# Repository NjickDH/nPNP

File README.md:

# nPNP

## Description
This project will aim to build a high speed and accurate pick and place machine using bldc motors as servo's, automatic feeders and vision. Currently work is being done on developing component feeders.

## Features
- __Automatic component feeders:__
  - Designed for use of tape with 8mm Tape and Reel specifications.
  - Uses a 40x40mm aluminium profile as rail for mounting with integrated usb port for automatic powering and communication with the feeders.
  - Capable of accepting 20 feeders on a 500mm long aluminium profile.
  - SMT Reel holder which makes use of full sized reels convenient.
  - Handle for ease of insertion/removal from aluminium rail.
  - UART over RS485 for easy and reliable communication with the feeders. This means all feeders are controllable using a single USB port with use of a USB-RS485 converter.
  - Two buttons for manual control of the motor driving the tape forwards and backwards.
  - RGB Status LED provides the user with the current status of each feeder.
  - Integrated IR sensor as rotary encoder for accurate repeatability of the motors movement.
  - Automatically and mechanically peels tape based on the movement of the tape itself to reduce complexity and part count.
  - 
-

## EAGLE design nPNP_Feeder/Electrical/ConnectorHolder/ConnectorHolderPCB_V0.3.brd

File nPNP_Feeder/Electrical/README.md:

# nPNP Feeder electrical

## Description
The schematic and board files for all PCB's for each feeder are placed here. Please read relevant notes for each of these boards below.

## Notes
- __MainFeeder:__
  - Schematic has MCU named as ATmega328-AU as this is the highest MCU in the pin compatible series. Actual MCU in the main feeder, and for which the firmware is written, is the ATmega48A. For more information about pin compatibility click [here](https://ww1.microchip.com/downloads/en/DeviceDoc/ATmega48A-PA-88A-PA-168A-PA-328-P-DS-DS40002061B.pdf) .
- __USBFeeder:__
  - This PCB has to be connected to the main feeder PCB by soldering 4 wires from the 4 pads on the USBFeeder PCB to the 4 pads on the main feeder PCB.
- __ConnectorHolder:__
  - This PCB is to be inserted into the 40x40mm aluminium profile. Two holes on each end are used for mounting the PCB inside the slot. An alumium profile with the following dimensions must be used:

### TODO:
- [x] Add BOM for each PCB
- [ ] Add price estimation for each PCB
- [ ] Validate MainFeederV1.0

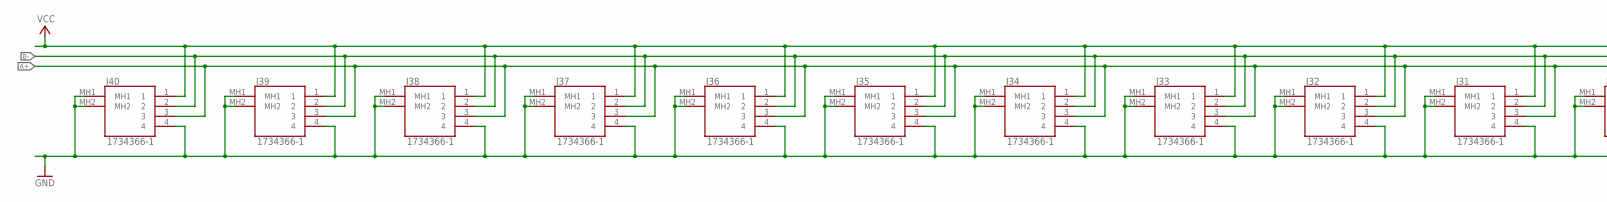
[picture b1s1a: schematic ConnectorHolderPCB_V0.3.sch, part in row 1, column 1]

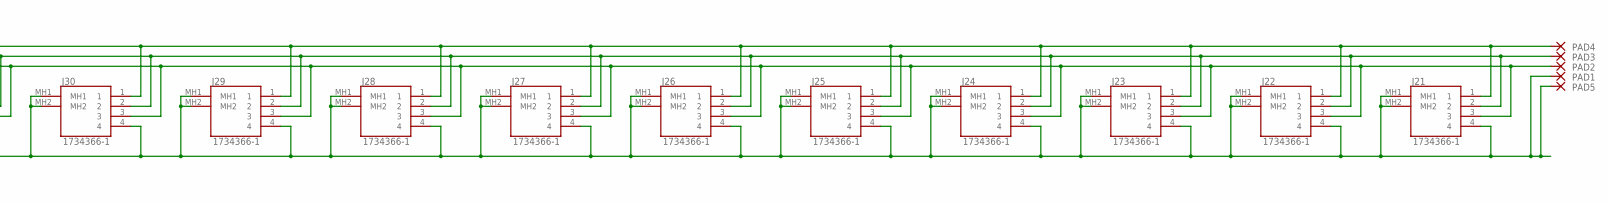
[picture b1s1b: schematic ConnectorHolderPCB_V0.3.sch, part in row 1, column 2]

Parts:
J21, J22, J23, J24, J25, J26, J27, J28, J29, J30, J31, J32, J33, J34, J35, J36, J37, J38, J39, J40: 1734366-1; 17343661
PAD1, PAD2, PAD3, PAD4, PAD5: SMD2; SMD1,27-2,54

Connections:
A+: J21.3, J22.3, J23.3, J24.3, J25.3, J26.3, J27.3, J28.3, J29.3, J30.3, J31.3, J32.3, J33.3, J34.3, J35.3, J36.3, J37.3, J38.3, J39.3, J40.3, PAD2.1
B-: J21.2, J22.2, J23.2, J24.2, J25.2, J26.2, J27.2, J28.2, J29.2, J30.2, J31.2, J32.2, J33.2, J34.2, J35.2, J36.2, J37.2, J38.2, J39.2, J40.2, PAD3.1
GND: J21.4, J21.MH1, J21.MH2, J22.4, J22.MH1, J22.MH2, J23.4, J23.MH1, J23.MH2, J24.4, J24.MH1, J24.MH2, J25.4, J25.MH1, J25.MH2, J26.4, J26.MH1, J26.MH2, J27.4, J27.MH1, J27.MH2, J28.4, J28.MH1, J28.MH2, J29.4, J29.MH1, J29.MH2, J30.4, J30.MH1, J30.MH2, J31.4, J31.MH1, J31.MH2, J32.4, J32.MH1, J32.MH2, J33.4, J33.MH1, J33.MH2, J34.4, J34.MH1, J34.MH2, J35.4, J35.MH1, J35.MH2, J36.4, J36.MH1, J36.MH2, J37.4, J37.MH1, J37.MH2, J38.4, J38.MH1, J38.MH2, J39.4, J39.MH1, J39.MH2, J40.4, J40.MH1, J40.MH2, PAD1.1, PAD5.1
VCC: J21.1, J22.1, J23.1, J24.1, J25.1, J26.1, J27.1, J28.1, J29.1, J30.1, J31.1, J32.1, J33.1, J34.1, J35.1, J36.1, J37.1, J38.1, J39.1, J40.1, PAD4.1

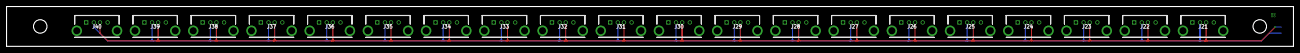
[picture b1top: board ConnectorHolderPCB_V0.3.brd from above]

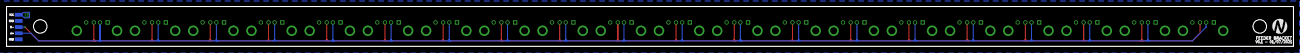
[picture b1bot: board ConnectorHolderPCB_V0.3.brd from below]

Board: 2 copper layers, 420.0 x 13.0 mm, 26 parts (6 on the bottom side), 4 nets.

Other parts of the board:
U$1: NPNP_LARGE_NOTEXT

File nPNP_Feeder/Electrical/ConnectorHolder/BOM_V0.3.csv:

Qty;Value;Device;Package;Parts;Description;DESCRIPTION;HEIGHT;MANUFACTURER_NAME;MANUFACTURER_PART_NUMBER;MOUSER_PART_NUMBER;MOUSER_PRICE-STOCK;POPULARITY
20;1734366-1;1734366-1;17343661;J21, J22, J23, J24, J25, J26, J27, J28, J29, J30, J31, J32, J33, J34, J35, J36, J37, J38, J39, J40;USB Connectors 1PORT 4POS VERT T/H USB 2.0 BLACK;USB Connectors 1PORT 4POS VERT T/H USB 2.0 BLACK;15mm;TE Connectivity;1734366-1;571-1734366-1;https://www.mouser.co.uk/ProductDetail/TE-Connectivity/17343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;

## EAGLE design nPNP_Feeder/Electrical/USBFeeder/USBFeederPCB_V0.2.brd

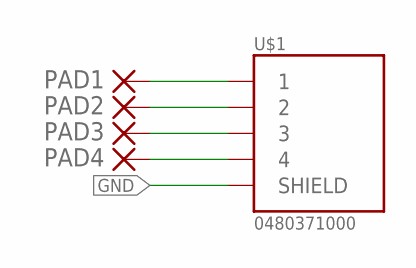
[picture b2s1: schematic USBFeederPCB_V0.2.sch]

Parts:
PAD1, PAD2, PAD3, PAD4: SMD2; SMD1,27-2,54
U$1: 0480371000

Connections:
GND: U$1.SHIELD1 (SHIELD), U$1.SHIELD2 (SHIELD)
unnamed: PAD1.1, U$1.1
unnamed: PAD2.1, U$1.2
unnamed: PAD3.1, U$1.3
unnamed: PAD4.1, U$1.4

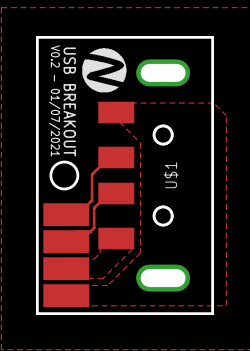
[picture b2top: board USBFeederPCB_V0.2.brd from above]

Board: 2 copper layers, 9.7 x 15.3 mm, 6 parts (0 on the bottom side), 5 nets.

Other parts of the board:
U$3: NPNP_SMALL_NOTEXT

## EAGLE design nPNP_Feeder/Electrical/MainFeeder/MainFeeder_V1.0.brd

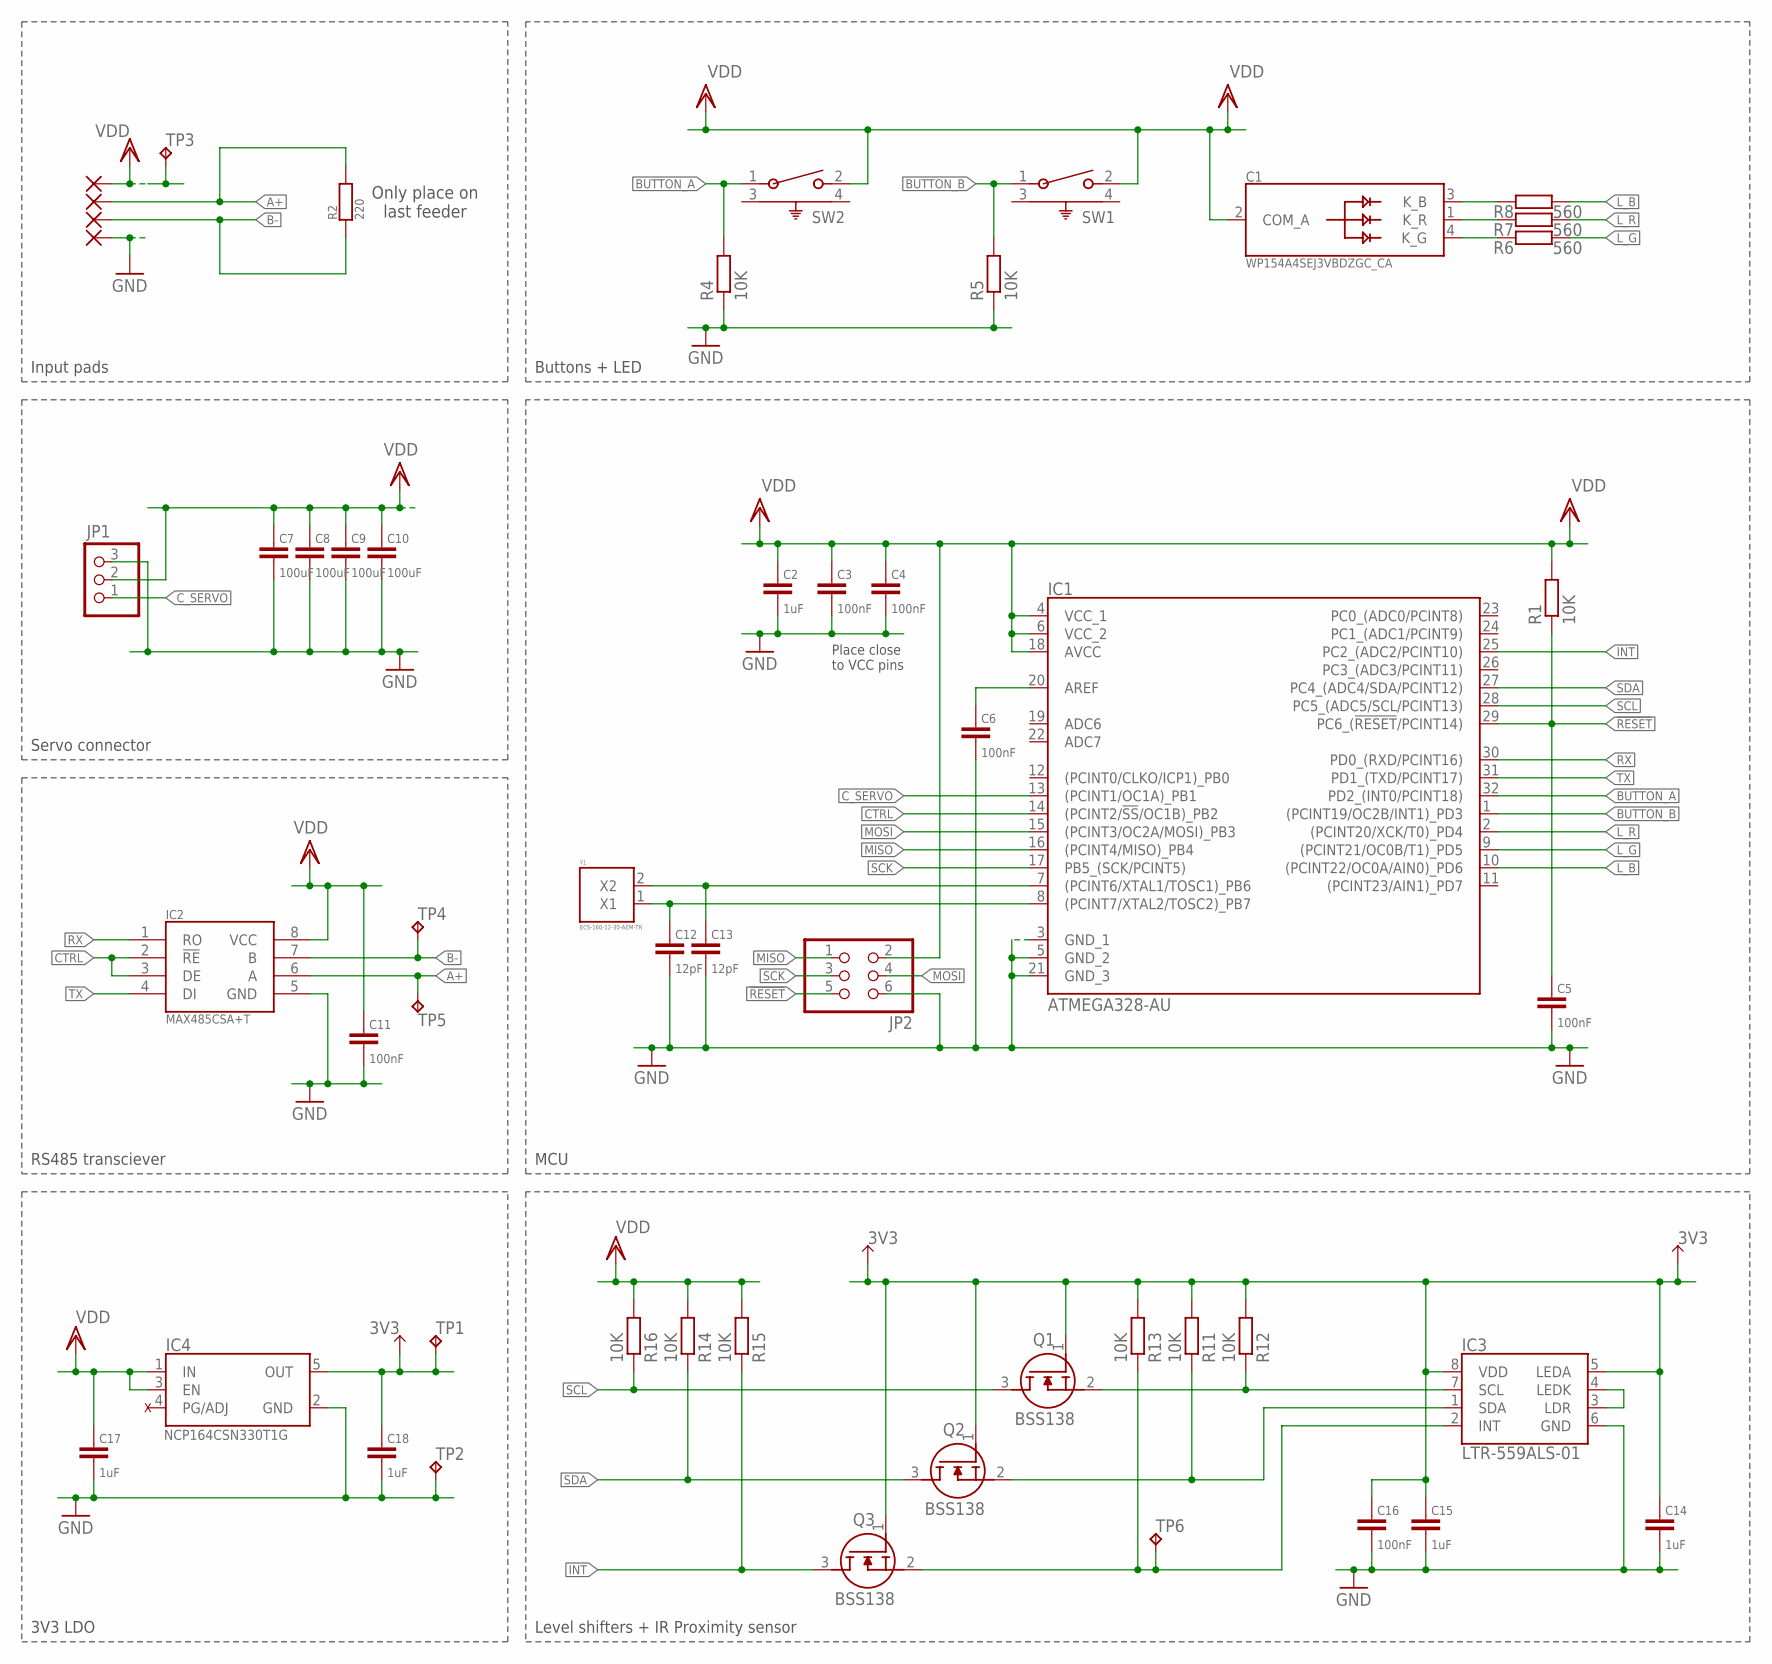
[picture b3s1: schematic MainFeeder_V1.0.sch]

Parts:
C1: WP154A4SEJ3VBDZGC_CA; L-154A4SUREQBFZGEC
C2, C14, C15, C17, C18: 1uF; C0603
C3, C4, C5, C6, C11, C16: 100nF; C0603
C7, C8, C9, C10: 100uF; C0805
C12, C13: 12pF; C0603
IC1: ATMEGA328-AU; QFP80P900X900X120-32N
IC2: MAX485CSA+T; SOIC127P600X175-8N
IC3: LTR-559ALS-01; LTR559ALS01
IC4: NCP164CSN330T1G; SOT95P275X110-5N
JP1: PINHD-1X3/90; 1X03/90
JP2: PINHD-2X3; 2X03
PAD1, PAD2, PAD3, PAD4: SMD2; SMD1,27-2,54
Q1, Q2, Q3: BSS138; SOT95P240X120-3N
R1, R4, R5, R11, R12, R13, R14, R15, R16: 10K; R0603
R2: 220; R0603
R6, R7, R8: 560; R0603
SW1, SW2: 1-1825027-1; SW2_1825027-A_TEC
TP1, TP2, TP3, TP4, TP5, TP6: TPB1,27; B1,27
Y1: ECS-160-12-30-AEM-TR; ECS1601230AEMTR

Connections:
3V3: C14.1, C15.1, C16.1, C18.1, IC3.5 (LEDA), IC3.8 (VDD), IC4.5 (OUT), Q1.1 (G), Q2.1 (G), Q3.1 (G), R11.2, R12.2, R13.2, TP1.TP
!RESET: C5.1, IC1.29 (PC6_(!RESET!/PCINT14)), JP2.5, R1.1
A+: IC2.6 (A), PAD1.1, R2.2, TP5.TP
B-: IC2.7 (B), PAD2.1, R2.1, TP4.TP
BUTTON_A: IC1.32 (PD2_(INT0/PCINT18)), R4.2, SW2.1
BUTTON_B: IC1.1 ((PCINT19/OC2B/INT1)_PD3), R5.2, SW1.1
CTRL: IC1.14 ((PCINT2/!SS!/OC1B)_PB2), IC2.2 (!RE), IC2.3 (DE)
C_SERVO: IC1.13 ((PCINT1/OC1A)_PB1), JP1.1
GND: C2.2, C3.2, C4.2, C5.2, C6.2, C7.2, C8.2, C9.2, C10.2, C11.2, C12.2, C13.2, C14.2, C15.2, C16.2, C17.2, C18.2, IC1.3 (GND_1), IC1.5 (GND_2), IC1.21 (GND_3), IC2.5 (GND), IC3.6 (GND), IC4.2 (GND), JP1.3, JP2.6, PAD3.1, R4.1, R5.1, TP2.TP
INT: IC1.25 (PC2_(ADC2/PCINT10)), Q3.3 (D), R15.1
INT_3V3: IC3.2 (INT), Q3.2 (S), R13.1, TP6.TP
L_B: IC1.10 ((PCINT22/OC0A/AIN0)_PD6), R8.1
L_G: IC1.9 ((PCINT21/OC0B/T1)_PD5), R6.1
L_R: IC1.2 ((PCINT20/XCK/T0)_PD4), R7.1
MISO: IC1.16 ((PCINT4/MISO)_PB4), JP2.1
MOSI: IC1.15 ((PCINT3/OC2A/MOSI)_PB3), JP2.4
unnamed: C6.1, IC1.20 (AREF)
unnamed: C1.3 (K_B), R8.2
unnamed: C1.1 (K_R), R7.2
unnamed: IC3.3 (LDR), IC3.4 (LEDK)
unnamed: C12.1, IC1.8 ((PCINT7/XTAL2/TOSC2)_PB7), Y1.1 (X1)
unnamed: C1.4 (K_G), R6.2
unnamed: C13.1, IC1.7 ((PCINT6/XTAL1/TOSC1)_PB6), Y1.2 (X2)
RX: IC1.30 (PD0_(RXD/PCINT16)), IC2.1 (RO)
SCK: IC1.17 (PB5_(SCK/PCINT5)), JP2.3
SCL: IC1.28 (PC5_(ADC5/SCL/PCINT13)), Q1.3 (D), R16.1
SCL_3V3: IC3.7 (SCL), Q1.2 (S), R12.1
SDA: IC1.27 (PC4_(ADC4/SDA/PCINT12)), Q2.3 (D), R14.1
SDA_3V3: IC3.1 (SDA), Q2.2 (S), R11.1
TX: IC1.31 (PD1_(TXD/PCINT17)), IC2.4 (DI)
VDD: C1.2 (COM_A), C2.1, C3.1, C4.1, C7.1, C8.1, C9.1, C10.1, C11.1, C17.1, IC1.4 (VCC_1), IC1.6 (VCC_2), IC1.18 (AVCC), IC2.8 (VCC), IC4.1 (IN), IC4.3 (EN), JP1.2, JP2.2, PAD4.1, R1.2, R14.2, R15.2, R16.2, SW1.2, SW2.2, TP3.TP

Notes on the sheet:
Input pads
Servo connector
Buttons + LED
Place close to VCC pins
MCU
RS485 transciever
Only place on last feeder
3V3 LDO
Level shifters + IR Proximity sensor

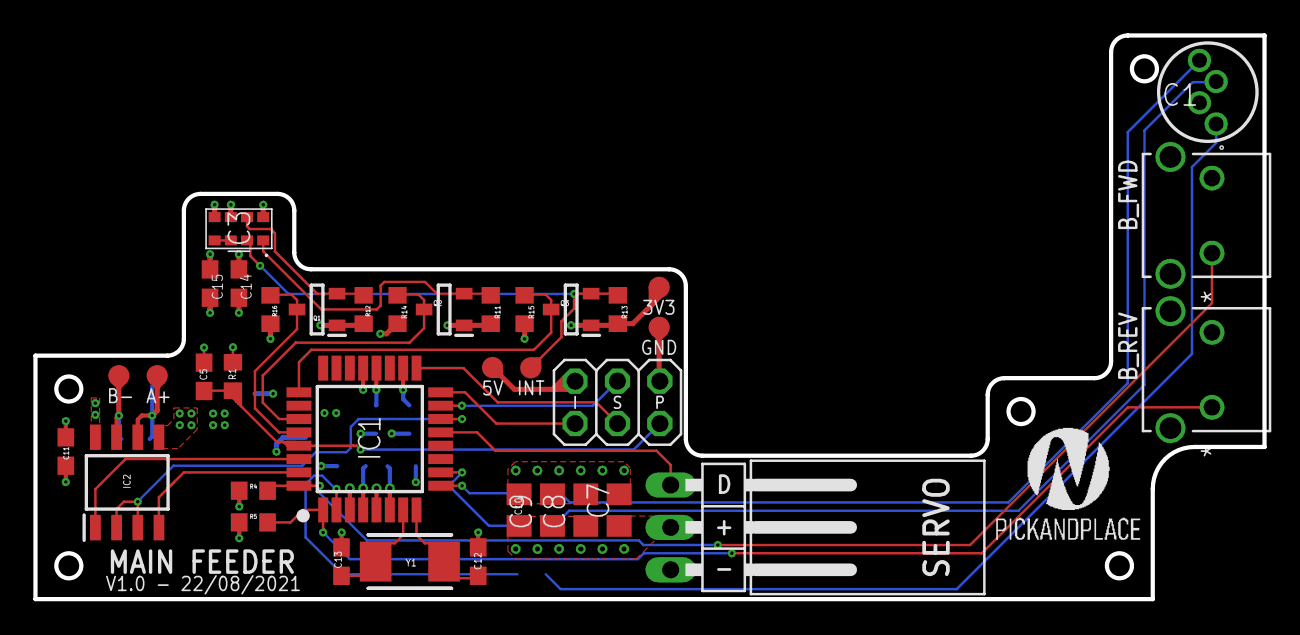
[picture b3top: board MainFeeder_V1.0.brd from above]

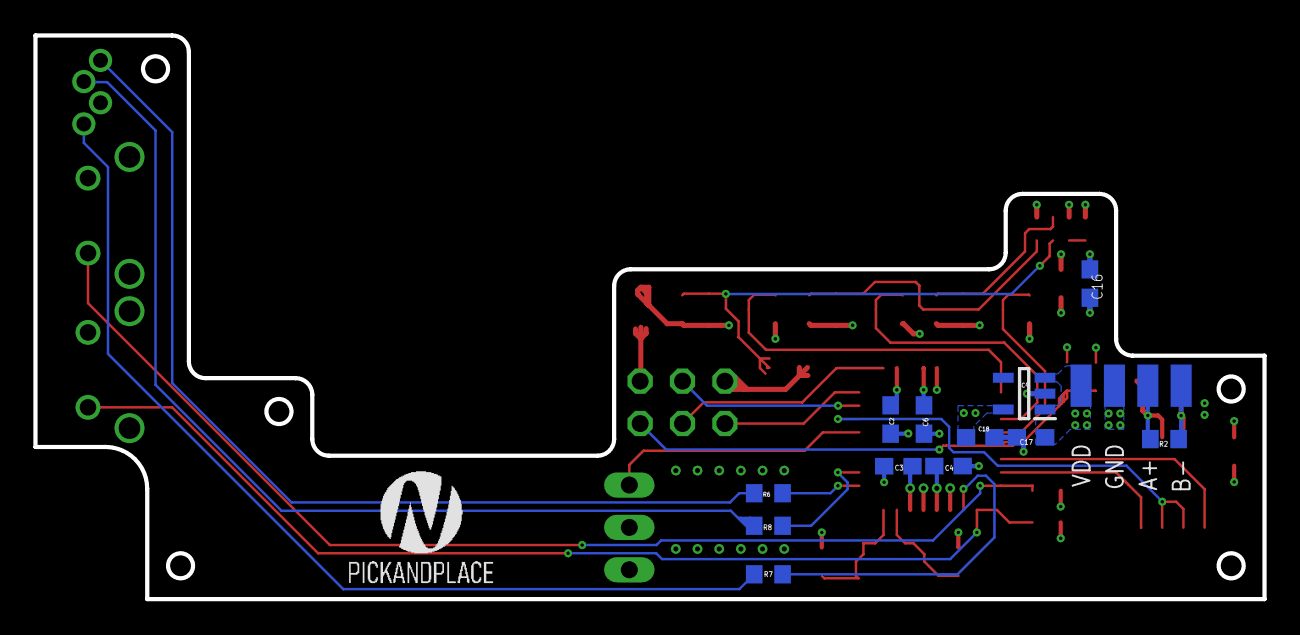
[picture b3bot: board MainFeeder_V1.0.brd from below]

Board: 4 copper layers, 73.7 x 33.8 mm, 55 parts (17 on the bottom side), 31 nets.

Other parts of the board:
U$2, U$3: NPNP_LARGE_TEXT

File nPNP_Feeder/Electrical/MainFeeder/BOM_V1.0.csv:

Qty;Value;Device;Package;Parts;Description;;;;;;
1;Generic;PINHD-1X3/90;1X03/90;JP1;PIN HEADER;;;;;;
1;Generic;PINHD-2X3;2X03;JP2;PIN HEADER;;;;;;
2;1-1825027-1;1-1825027-1;SW2_1825027-A_TEC;SW1, SW2;Button;;;;;;
6;100nF;C-EUC0603;C0603;C3, C4, C5, C6, C11, C16;CAPACITOR, European symbol;;;;;;
4;100uF;C-EUC0805;C0805;C7, C8, C9, C10;CAPACITOR, European symbol;;;;;;
9;10K;R-EU_R0603;R0603;R1, R4, R5, R11, R12, R13, R14, R15, R16;RESISTOR, European symbol;;;;;;
2;12pF;C-EUC0603;C0603;C12, C13;CAPACITOR, European symbol;;;;;;
5;1uF;C-EUC0603;C0603;C2, C14, C15, C17, C18;CAPACITOR, European symbol;;;;;;
1;220;R-EU_R0603;R0603;R2;RESISTOR, European symbol;;;;;;
3;560;R-EU_R0603;R0603;R6, R7, R8;RESISTOR, European symbol;;;;;;
1;ATMEGA328-AU;ATMEGA328-AU;QFP80P900X900X120-32N;IC1;MCU 8-Bit AVR 32KB Flash 2.5/3.3/5V ATMEGA328-AU, 8 bit AVR Microcontroller 20MHz 32 kB Flash, 1 kB, 2 kB RAM, I2C 32-Pin TQFP;;;;;;
3;BSS138;BSS138;SOT95P240X120-3N;Q1, Q2, Q3;N-channel MOSFET,BSS138 0.2A 50V;;;;;;
1;ECS-160-12-30-AEM-TR;ECS-160-12-30-AEM-TR;ECS1601230AEMTR;Y1;ECX-53 SMD CRYSTAL;;;;;;
1;LTR-559ALS-01;LTR-559ALS-01;LTR559ALS01;IC3;Light to Digital Converters Ambient Light Photo Sensor;;;;;;
1;MAX485CSA+T;MAX485CSA+T;SOIC127P600X175-8N;IC2;RS-422/RS-485 Interface IC Low-Power, Slew-Rate-Limited RS-485/RS-422 Transceivers;;;;;;
1;NCP164CSN330T1G;NCP164CSN330T1G;SOT95P275X110-5N;IC4;LDO Regulator Pos 3.3V 0.3A 5-Pin TSOP T/R;;;;;;
1;WP154A4SEJ3VBDZGC_CA;WP154A4SEJ3VBDZGC_CA;L-154A4SUREQBFZGEC;C1;Standard LEDs - Through Hole 5MM RGB LED;;;;;;
;;;;;;;;;;;
;;;;;;;;;;;

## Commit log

2021-08-24 Initial README setup
    Added README banner and initial project information
2021-08-25 Initial feeder firmware
    All peripherals tested and working
2021-08-25 Feeder schematic and board files
2021-08-29 Added BOM, schematic as pdf and PCB as image
2021-09-04 POC of PWM with IR encoder feedback
2021-09-04 Change img name
2021-09-22 Global BOM start and BOM for MainFeederV1.0
2021-09-22 Test for aluminium encoder disk using SerialPlot
2021-09-24 POC PID Control based on encoder disk feedback
2021-09-24 Self configure LTR559 interrupt threshold
2021-09-25 Self configured value now saved in EEPROM and loaded upon startup
2021-09-25 Initial feeder protocol implemented

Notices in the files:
parts and their libraries:
COPYRIGHT: Copyright (C) 2016 Accelerated Designs. All rights reserved
